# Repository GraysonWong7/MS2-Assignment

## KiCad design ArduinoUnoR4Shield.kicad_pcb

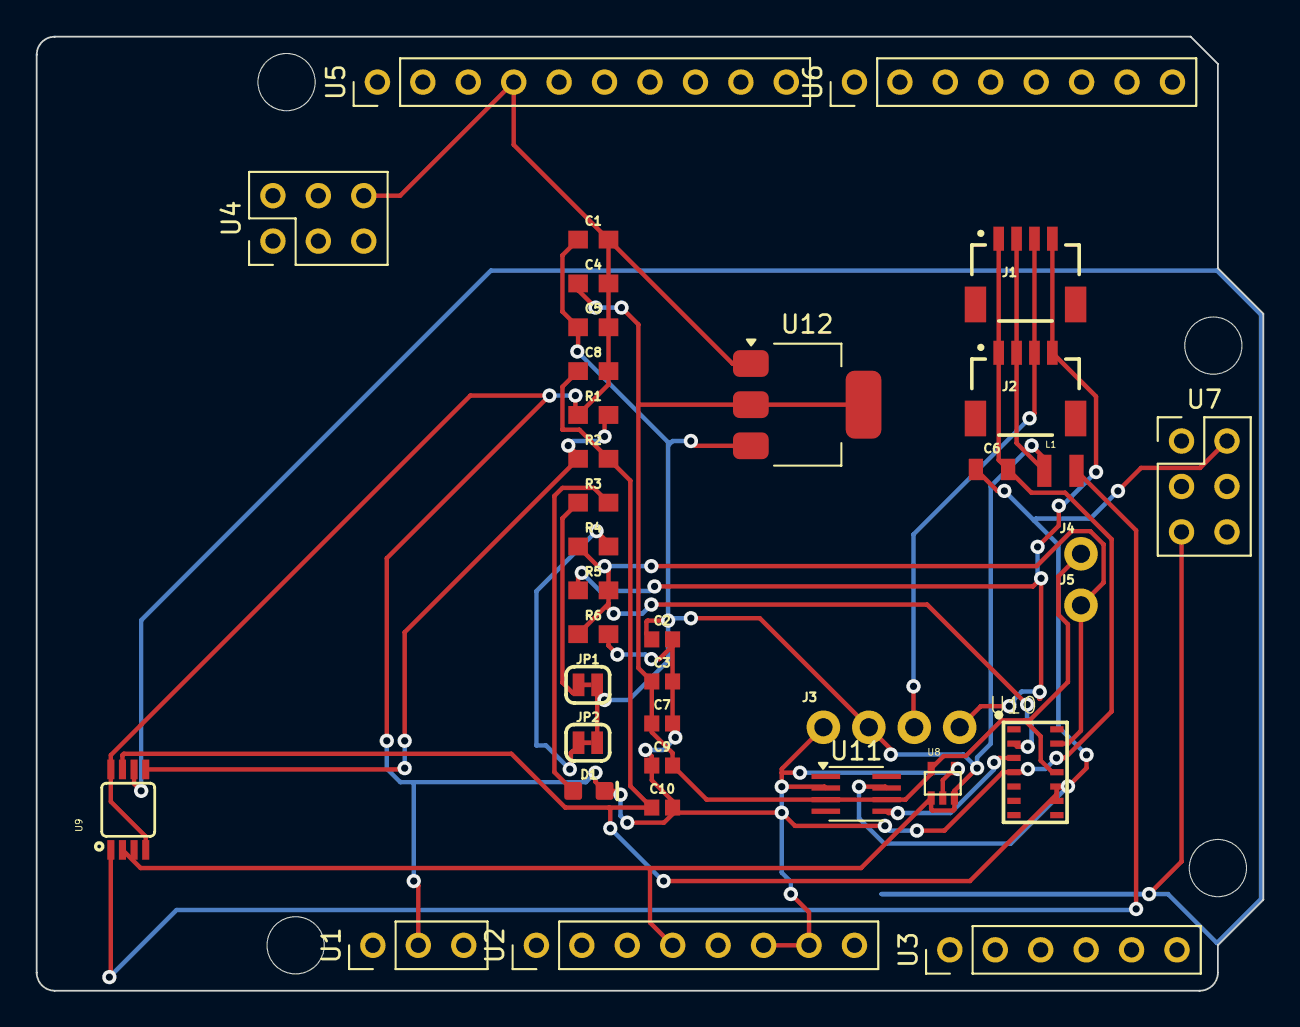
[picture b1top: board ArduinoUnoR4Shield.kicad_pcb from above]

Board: 2 copper layers, 68.6 x 53.3 mm, 41 parts (0 on the bottom side), 13 nets.

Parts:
C1, C4, C5, C8: 10uF; 0603
C2, C3, C7, C9, C10: 0.1uF; 0402
C6: 22uF; 0805
D1: RED; LED-0603
H1, H2, H3, H4: MountingHole_Arduino; Arduino_MountingHole
J1, J2: QWIIC_RA; JST04_1MM_RA
J3: PTH; 1X04_NO_SILK
J4, J5: CONN_01PTH_NO_SILK_YES_STOP; 1X01_NO_SILK
JP1: LED; SMT-JUMPER_2_NC_TRACE_SILK
JP2: INT; SMT-JUMPER_2_NC_TRACE_SILK
L1: 2.2μH; 0806
R1: 100k; 0603
R2: 750K; 0603
R3: 1k; 0603
R4: 4.7k; 0603
R5: 3.2k; 0603
R6: 1.8k; 0603
U1: Arduino_Header_OFF; Arduino_PinSocket_1x03_P2.54mm_Vertical
U2: Arduino_Header_Analog_1; Arduino_PinSocket_1x08_P2.54mm_Vertical
U3: Arduino_Header_Analog_2; Arduino_PinSocket_1x06_P2.54mm_Vertical
U4: Arduino_Header_ESP32-S3; Arduino_PinSocket_2x03_P2.54mm_Vertical
U5: Arduino_Header_Digital_1; Arduino_PinSocket_1x10_P2.54mm_Vertical
U6: Arduino_Header_Digital_2; Arduino_PinSocket_1x08_P2.54mm_Vertical
U7: Arduino_Header_ICSP; Arduino_PinSocket_2x03_P2.54mm_Vertical
U8: 1.8V/100mA; SC70
U9: PAM2401; MSOP8
U10: MAX30101EFD; 14_PIN_OESIP
U11: TXS0102DCT; SSOP-8_2.95x2.8mm_P0.65mm
U12: LD1117S18TR_SOT223; SOT-223-3_TabPin2

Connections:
1.8V: C3.1, C4.1, C7.1, C9.2, J4.1, U8.5 (OUT), U10.P11 (VDD), U11.3 (VCCA), U11.6 (OE), U12.2 (VO)
3.3V: C1.1, C2.1, C5.1, J1.2, J2.2, J3.2, JP1.2, JP2.2, L1.1, U2.4 (+3V3), U8.1 (IN), U8.3 (EN), U9.2 (EN), U9.3 (VIN), U12.3 (VI)
5V: C6.1, C8.1, C10.1, R2.2, U7.2 (+5V), U9.7 (OUT), U10.P9 (VDD_LED), U10.P10 (VDD_LED), U11.7 (VCCB)
/SDA: J1.3, J2.3, J3.3
GND: C1.2, C2.2, C3.2, C4.2, C5.2, C6.2, C7.2, C8.2, C9.1, C10.2, D1.C, J1.1, J2.1, J3.1, R1.1, R6.2, U1.2 (GND), U2.6 (GND), U2.7 (GND), U4.6 (GND), U5.4 (GND), U8.2 (GND), U8.4 (BP), U9.4 (AGND), U9.8 (PGND), U10.P4 (GND), U10.P12 (GND), U11.2 (GND), U12.1 (GND)
LV_INT: J5.1, R4.1, R5.2, R6.1, U10.P2 (SCL), U10.P3 (SDA), U10.P13 (~INT), U11.1 (B2), U11.4 (A2), U11.5 (A1)
MC_SCL: J1.4, J2.4, J3.4, R5.1
unnamed: D1.A, R3.2
unnamed: JP1.1, R3.1
unnamed: JP2.1, R4.2
unnamed: U7.5 (RESET), U9.6 (RSET)
unnamed: R1.2, R2.1, U9.5 (FB)
unnamed: L1.2, U9.1 (LX)
